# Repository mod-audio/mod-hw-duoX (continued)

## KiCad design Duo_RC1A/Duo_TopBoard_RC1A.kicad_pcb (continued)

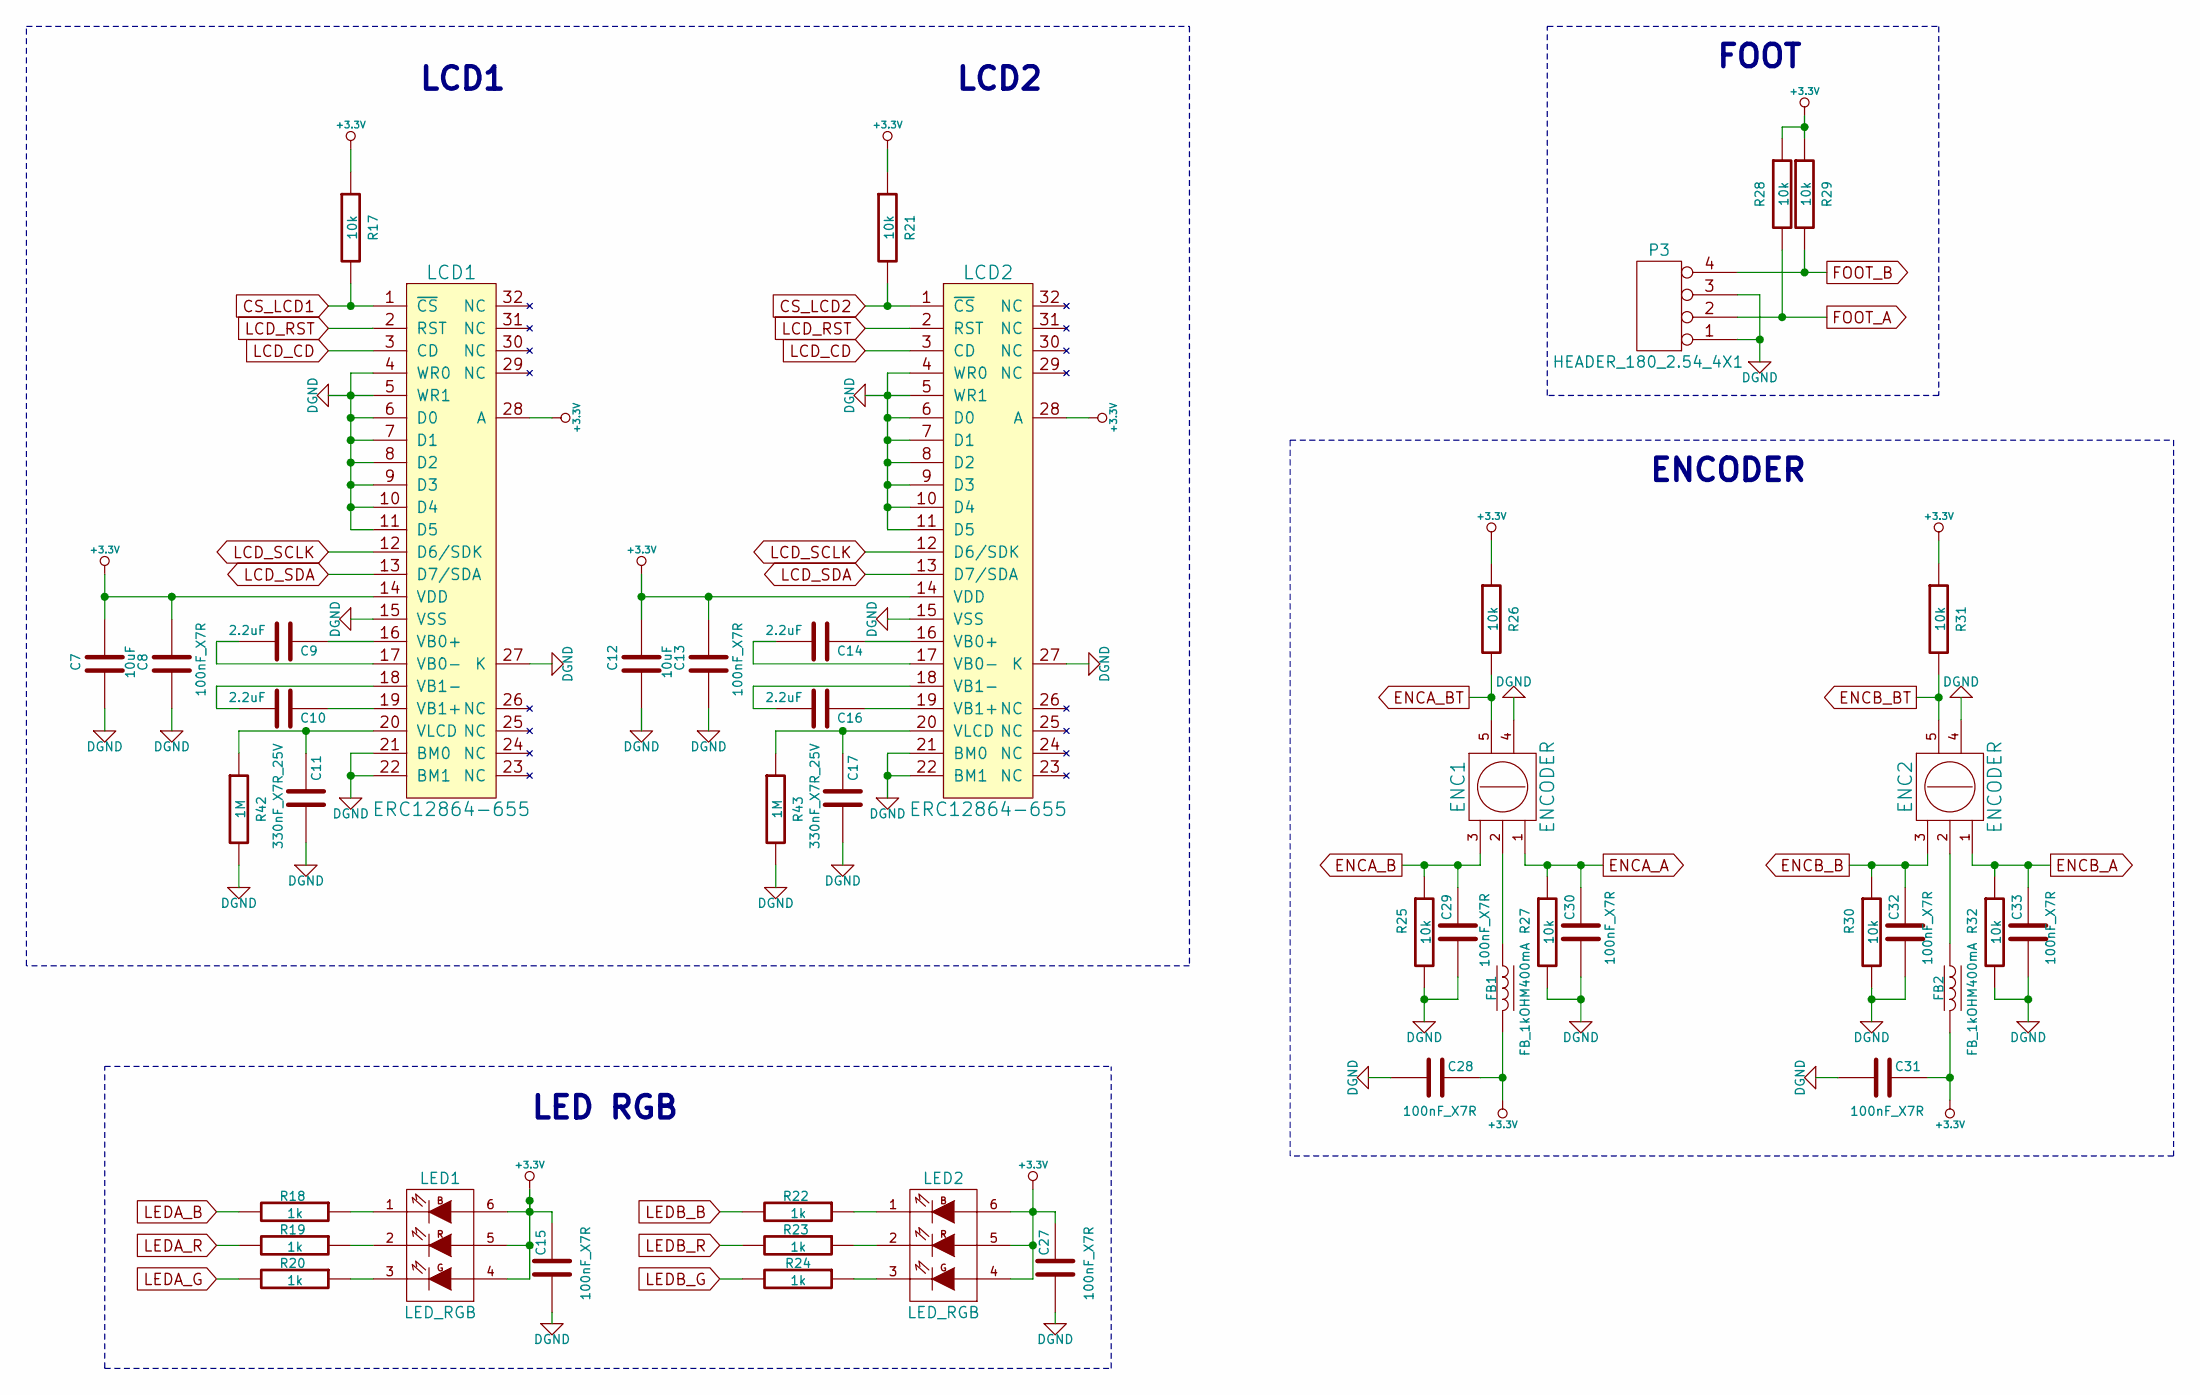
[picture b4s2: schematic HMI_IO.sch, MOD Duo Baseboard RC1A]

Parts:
C7, C12: 10uF; SM0603
C8, C13, C15, C27, C28, C29, C30, C31, C32, C33: 100nF_X7R; SM0603
C9, C10, C14, C16: 2.2uF; SM0603
C11, C17: 330nF_X7R_25V; SM0603
ENC1, ENC2: ENCODER; ENCODER_PEC11R-4xxxF-Sxxxx
FB1, FB2: FB_1kOHM400mA; SM0805
LCD1, LCD2: ERC12864-655
LED1, LED2: LED_RGB; LED_CLRTB_GFSF_1
P3: HEADER_180_2.54_4X1; Pin_Header_180_2.54_1x4
R17, R21, R25, R26, R27, R28, R29, R30, R31, R32: 10k; SM0603
R18, R19, R20, R22, R23, R24: 1k; SM0603
R42, R43: 1M; SM0603

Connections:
+3.3V: C7.1, C8.1, C12.1, C13.1, C15.1, C27.1, C28.1, C31.1, FB1.1, FB2.1, LCD1.14 (VDD), LCD1.28 (A), LCD2.14 (VDD), LCD2.28 (A), LED1.4 (KB), LED1.5 (KG), LED1.6 (KR), LED2.4 (KB), LED2.5 (KG), LED2.6 (KR), R17.1, R21.1, R26.1, R28.1, R29.1, R31.1; also elsewhere on the board
CS_LCD1: LCD1.1 (~CS), R17.2; also elsewhere on the board
CS_LCD2: LCD2.1 (~CS), R21.2; also elsewhere on the board
DGND: C7.2, C8.2, C11.2, C12.2, C13.2, C15.2, C17.2, C27.2, C28.2, C29.2, C30.2, C31.2, C32.2, C33.2, ENC1.4, ENC2.4, LCD1.4 (WR0), LCD1.5 (WR1), LCD1.6 (D0), LCD1.7 (D1), LCD1.8 (D2), LCD1.9 (D3), LCD1.10 (D4), LCD1.11 (D5), LCD1.15 (VSS), LCD1.21 (BM0), LCD1.22 (BM1), LCD1.27 (K), LCD2.4 (WR0), LCD2.5 (WR1), LCD2.6 (D0), LCD2.7 (D1), LCD2.8 (D2), LCD2.9 (D3), LCD2.10 (D4), LCD2.11 (D5), LCD2.15 (VSS), LCD2.21 (BM0), LCD2.22 (BM1), LCD2.27 (K), P3.1, P3.3, R25.2, R27.2, R30.2, R32.2, R42.2, R43.2; also elsewhere on the board
ENCA_A: C30.1, ENC1.1, R27.1; also elsewhere on the board
ENCA_B: C29.1, ENC1.3, R25.1; also elsewhere on the board
ENCA_BT: ENC1.5, R26.2; also elsewhere on the board
ENCB_A: C33.1, ENC2.1, R32.1; also elsewhere on the board
ENCB_B: C32.1, ENC2.3, R30.1; also elsewhere on the board
ENCB_BT: ENC2.5, R31.2; also elsewhere on the board
FOOT_A: P3.2, R28.2; also elsewhere on the board
FOOT_B: P3.4, R29.2; also elsewhere on the board
LCD_CD: LCD1.3 (CD), LCD2.3 (CD); also elsewhere on the board
LCD_RST: LCD1.2 (RST), LCD2.2 (RST); also elsewhere on the board
LCD_SCLK: LCD1.12 (D6/SDK), LCD2.12 (D6/SDK); also elsewhere on the board
LCD_SDA: LCD1.13 (D7/SDA), LCD2.13 (D7/SDA); also elsewhere on the board
LEDA_B: R18.2; also elsewhere on the board
LEDA_G: R20.2; also elsewhere on the board
LEDA_R: R19.2; also elsewhere on the board
LEDB_B: R22.2; also elsewhere on the board
LEDB_G: R24.2; also elsewhere on the board
LEDB_R: R23.2; also elsewhere on the board
unnamed: C9.1, LCD1.16 (VB0+)
unnamed: C9.2, LCD1.17 (VB0-)
unnamed: C10.1, LCD1.19 (VB1+)
unnamed: C10.2, LCD1.18 (VB1-)
unnamed: C11.1, LCD1.20 (VLCD), R42.1
unnamed: C14.1, LCD2.16 (VB0+)
unnamed: C14.2, LCD2.17 (VB0-)
unnamed: C16.1, LCD2.19 (VB1+)
unnamed: C16.2, LCD2.18 (VB1-)
unnamed: C17.1, LCD2.20 (VLCD), R43.1
unnamed: ENC1.2, FB1.2
unnamed: ENC2.2, FB2.2
unnamed: LED1.1 (AR), R18.1
unnamed: LED1.2 (AG), R19.1
unnamed: LED1.3 (AB), R20.1
unnamed: LED2.1 (AR), R22.1
unnamed: LED2.2 (AG), R23.1
unnamed: LED2.3 (AB), R24.1

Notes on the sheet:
LED RGB
ENCODER
FOOT
LCD2
LCD1

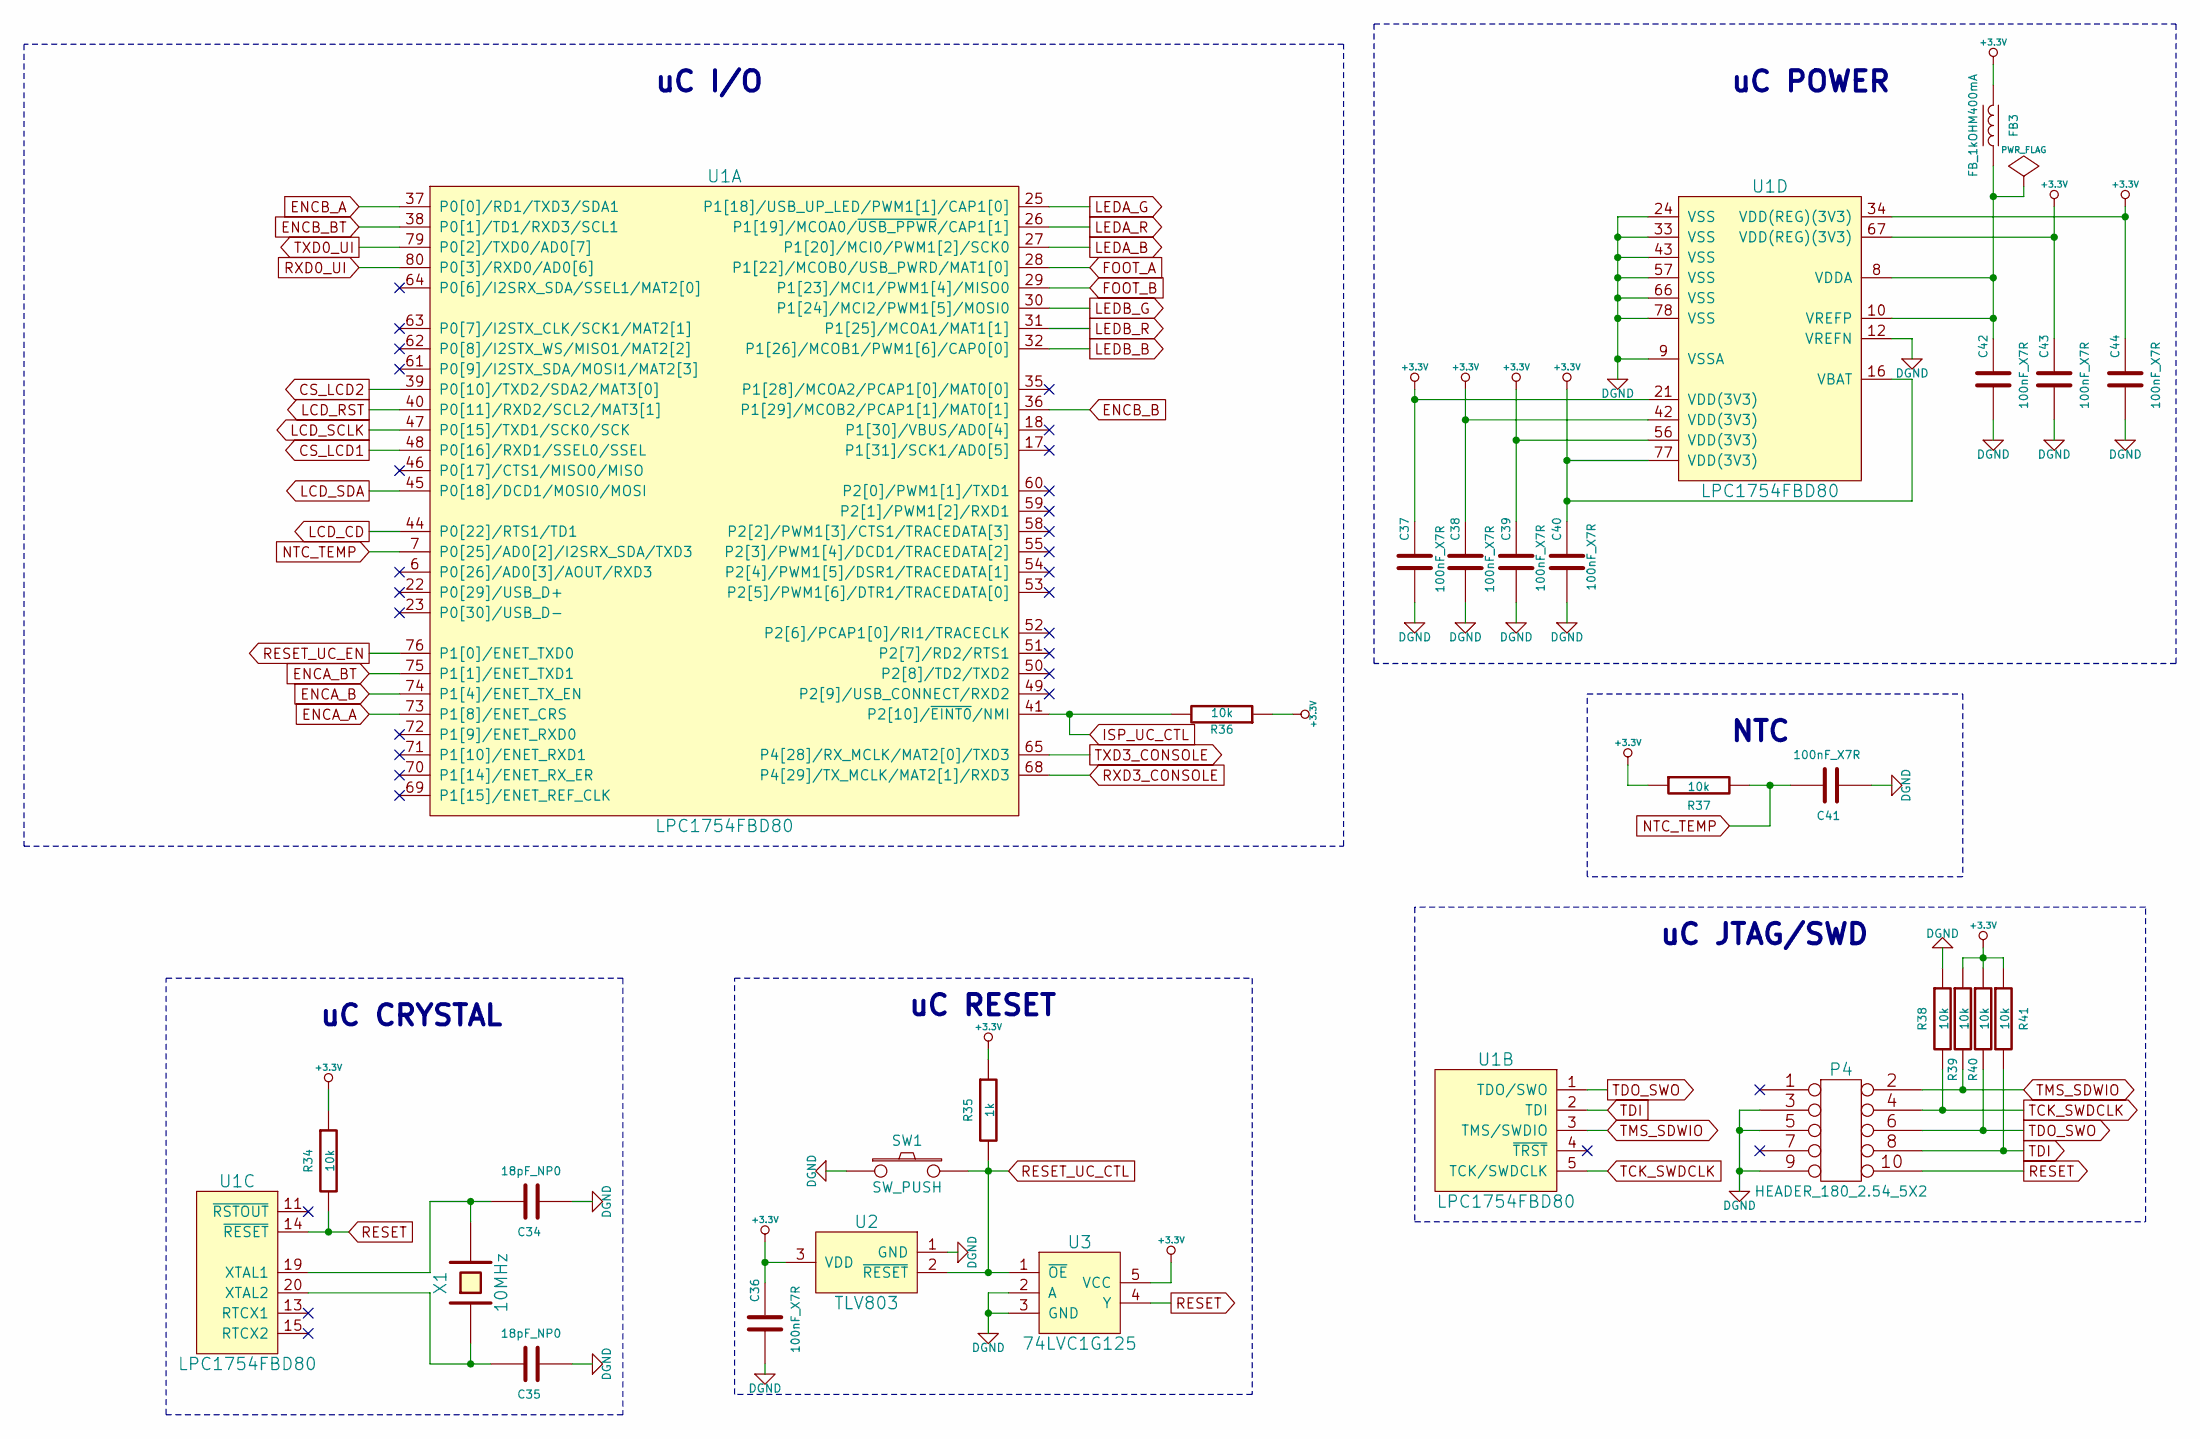
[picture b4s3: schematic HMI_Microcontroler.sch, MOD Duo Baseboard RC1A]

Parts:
C34, C35: 18pF_NP0; SM0603
C36, C37, C38, C39, C40, C41, C42, C43, C44: 100nF_X7R; SM0603
FB3: FB_1kOHM400mA; SM0805
P4: HEADER_180_2.54_5X2; Pin_Header_180_2.54_2x5
R34, R36, R37, R38, R39, R40, R41: 10k; SM0603
R35: 1k; SM0603
SW1: SW_PUSH; SWITCH_SMD_FSMSM
U1: LPC1754FBD80; LQFP80
U2: TLV803; SOT23
U3: 74LVC1G125; SOT353
X1: 10MHz; HC_49US

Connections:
+3.3V: C36.1, C37.1, C38.1, C39.1, C40.1, C43.1, C44.1, FB3.1, R34.1, R35.1, R36.1, R37.1, R39.1, R40.1, R41.1, U1.16 (VBAT), U1.21 (VDD(3V3)), U1.34 (VDD(REG)(3V3)), U1.42 (VDD(3V3)), U1.56 (VDD(3V3)), U1.67 (VDD(REG)(3V3)), U1.77 (VDD(3V3)), U2.3 (VDD), U3.5 (VCC); also elsewhere on the board
CS_LCD1: U1.48 (P0[16]/RXD1/SSEL0/SSEL); also elsewhere on the board
CS_LCD2: U1.39 (P0[10]/TXD2/SDA2/MAT3[0]); also elsewhere on the board
DGND: C34.2, C35.2, C36.2, C37.2, C38.2, C39.2, C40.2, C41.2, C42.2, C43.2, C44.2, P4.3, P4.5, P4.9, R38.1, SW1.1, U1.9 (VSSA), U1.12 (VREFN), U1.24 (VSS), U1.33 (VSS), U1.43 (VSS), U1.57 (VSS), U1.66 (VSS), U1.78 (VSS), U2.1 (GND), U3.2 (A), U3.3 (GND); also elsewhere on the board
ENCA_A: U1.73 (P1[8]/ENET_CRS); also elsewhere on the board
ENCA_B: U1.74 (P1[4]/ENET_TX_EN); also elsewhere on the board
ENCA_BT: U1.75 (P1[1]/ENET_TXD1); also elsewhere on the board
ENCB_A: U1.37 (P0[0]/RD1/TXD3/SDA1); also elsewhere on the board
ENCB_B: U1.36 (P1[29]/MCOB2/PCAP1[1]/MAT0[1]); also elsewhere on the board
ENCB_BT: U1.38 (P0[1]/TD1/RXD3/SCL1); also elsewhere on the board
FOOT_A: U1.28 (P1[22]/MCOB0/USB_PWRD/MAT1[0]); also elsewhere on the board
FOOT_B: U1.29 (P1[23]/MCI1/PWM1[4]/MISO0); also elsewhere on the board
ISP_UC_CTL: R36.2, U1.41 (P2[10]/~EINT0~/NMI); also elsewhere on the board
LCD_CD: U1.44 (P0[22]/RTS1/TD1); also elsewhere on the board
LCD_RST: U1.40 (P0[11]/RXD2/SCL2/MAT3[1]); also elsewhere on the board
LCD_SCLK: U1.47 (P0[15]/TXD1/SCK0/SCK); also elsewhere on the board
LCD_SDA: U1.45 (P0[18]/DCD1/MOSI0/MOSI); also elsewhere on the board
LEDA_B: U1.27 (P1[20]/MCI0/PWM1[2]/SCK0); also elsewhere on the board
LEDA_G: U1.25 (P1[18]/USB_UP_LED/PWM1[1]/CAP1[0]); also elsewhere on the board
LEDA_R: U1.26 (P1[19]/MCOA0/~USB_PPWR~/CAP1[1]); also elsewhere on the board
LEDB_B: U1.32 (P1[26]/MCOB1/PWM1[6]/CAP0[0]); also elsewhere on the board
LEDB_G: U1.30 (P1[24]/MCI2/PWM1[5]/MOSI0); also elsewhere on the board
LEDB_R: U1.31 (P1[25]/MCOA1/MAT1[1]); also elsewhere on the board
NTC_TEMP: C41.1, R37.2, U1.7 (P0[25]/AD0[2]/I2SRX_SDA/TXD3); also elsewhere on the board
unnamed: C34.1, U1.19 (XTAL1), X1.2
unnamed: C35.1, U1.20 (XTAL2), X1.1
unnamed: C42.1, FB3.2, U1.8 (VDDA), U1.10 (VREFP)
RESET: P4.10, R34.2, U1.14 (~RESET), U3.4 (Y)
RESET_UC_CTL: R35.2, SW1.2, U2.2 (~RESET), U3.1 (~OE); also elsewhere on the board
RESET_UC_EN: U1.76 (P1[0]/ENET_TXD0); also elsewhere on the board
RXD0_UI: U1.80 (P0[3]/RXD0/AD0[6]); also elsewhere on the board
RXD3_CONSOLE: U1.68 (P4[29]/TX_MCLK/MAT2[1]/RXD3); also elsewhere on the board
TCK_SWDCLK: P4.4, R38.2, U1.5 (TCK/SWDCLK)
TDI: P4.8, R41.2, U1.2 (TDI)
TDO_SWO: P4.6, R40.2, U1.1 (TDO/SWO)
TMS_SDWIO: P4.2, R39.2, U1.3 (TMS/SWDIO)
TXD0_UI: U1.79 (P0[2]/TXD0/AD0[7]); also elsewhere on the board
TXD3_CONSOLE: U1.65 (P4[28]/RX_MCLK/MAT2[0]/TXD3); also elsewhere on the board

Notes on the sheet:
uC JTAG/SWD
uC RESET
uC CRYSTAL
uC POWER
uC I/O
NTC

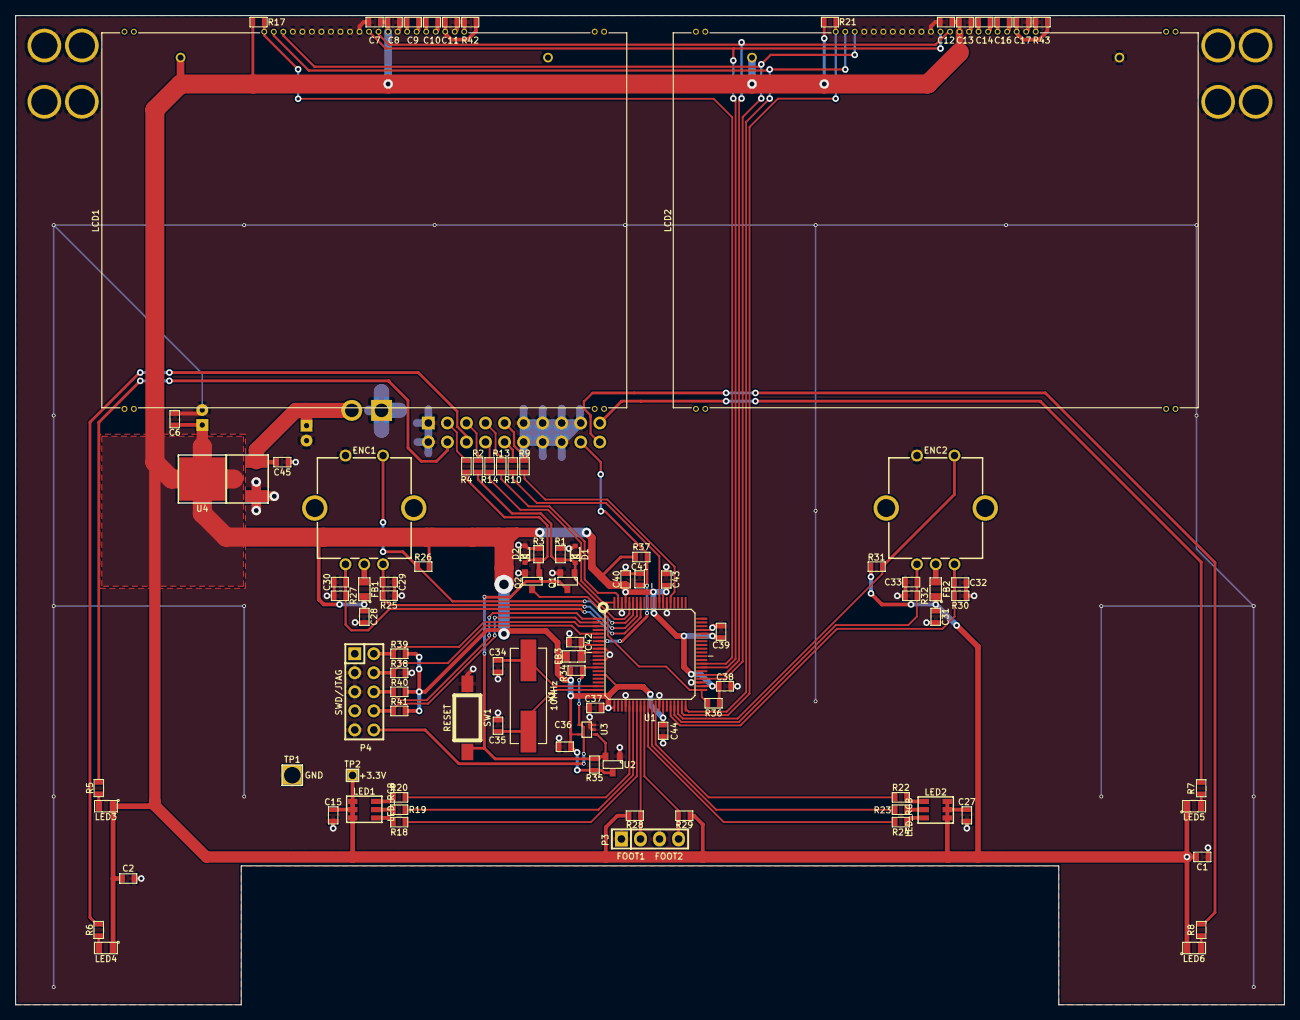
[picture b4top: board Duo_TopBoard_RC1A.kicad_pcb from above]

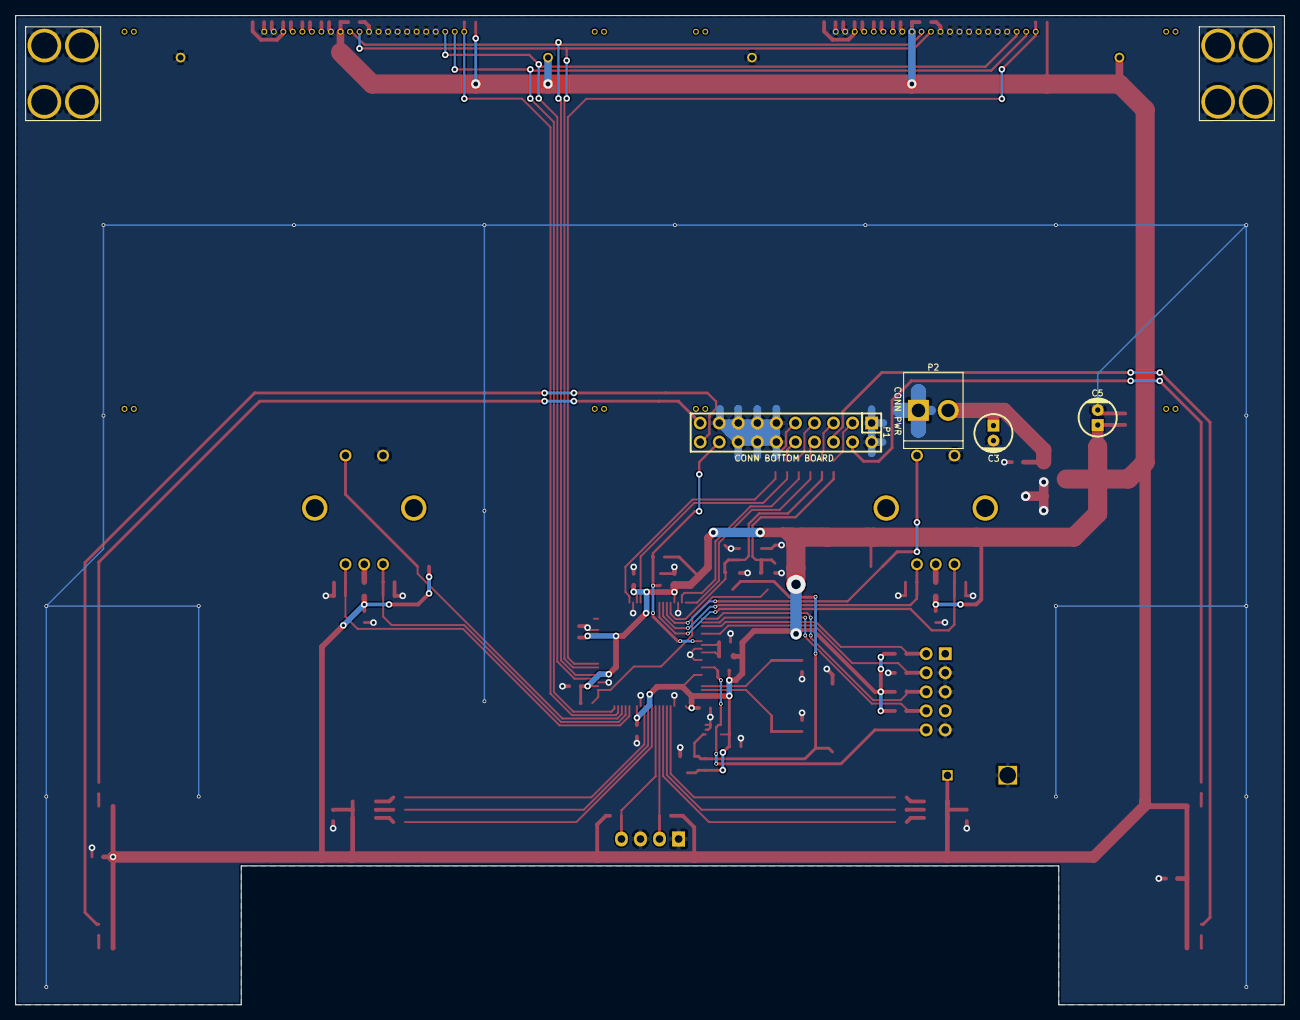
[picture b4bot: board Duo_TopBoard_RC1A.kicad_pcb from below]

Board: 2 copper layers, 169.2 x 131.9 mm, 104 parts (6 on the bottom side), 72 nets.

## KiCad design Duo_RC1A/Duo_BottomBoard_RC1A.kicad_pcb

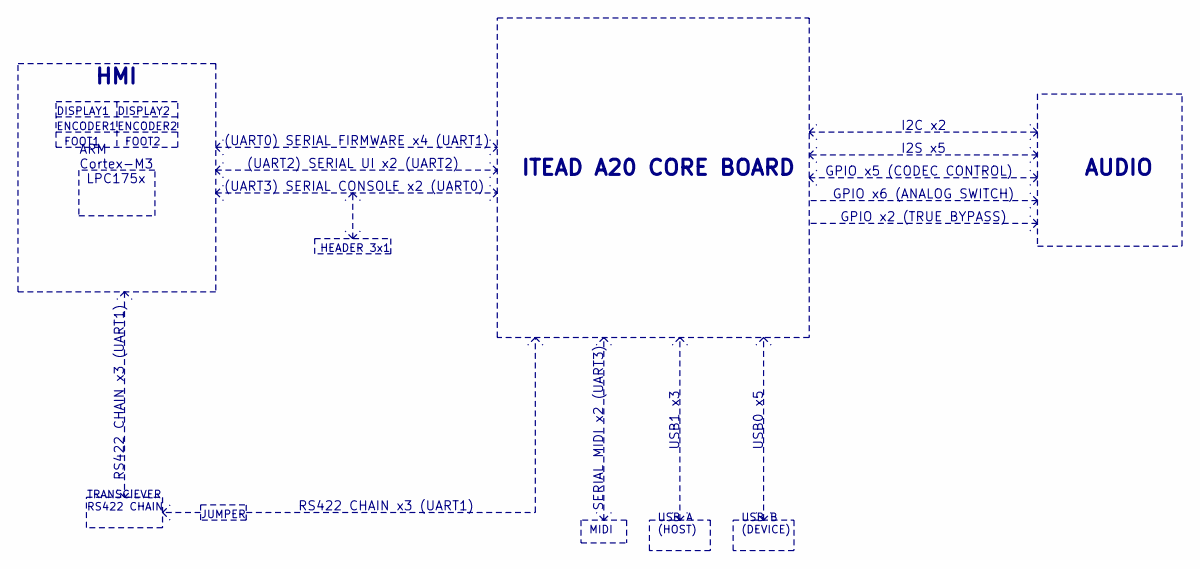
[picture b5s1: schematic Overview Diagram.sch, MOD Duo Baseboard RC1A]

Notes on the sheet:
ITEAD A20 CORE BOARD
ARM Cortex-M3 LPC175x
I2S x5
(UART0) SERIAL FIRMWARE x4 (UART1)
(UART2) SERIAL UI x2 (UART2)
HEADER 3x1
RS422 CHAIN x3 (UART1)
I2C x2
GPIO x6 (ANALOG SWITCH)
GPIO x2 (TRUE BYPASS)
(UART3) SERIAL CONSOLE x2 (UART0)
MIDI
SERIAL MIDI x2 (UART3)
DISPLAY1
DISPLAY2
FOOT1
FOOT2
ENCODER1
ENCODER2
HMI
TRANSCIEVER RS422 CHAIN
USB A (HOST)
USB B (DEVICE)
USB1 x3
USB0 x5
GPIO x5 (CODEC CONTROL)
AUDIO
JUMPER

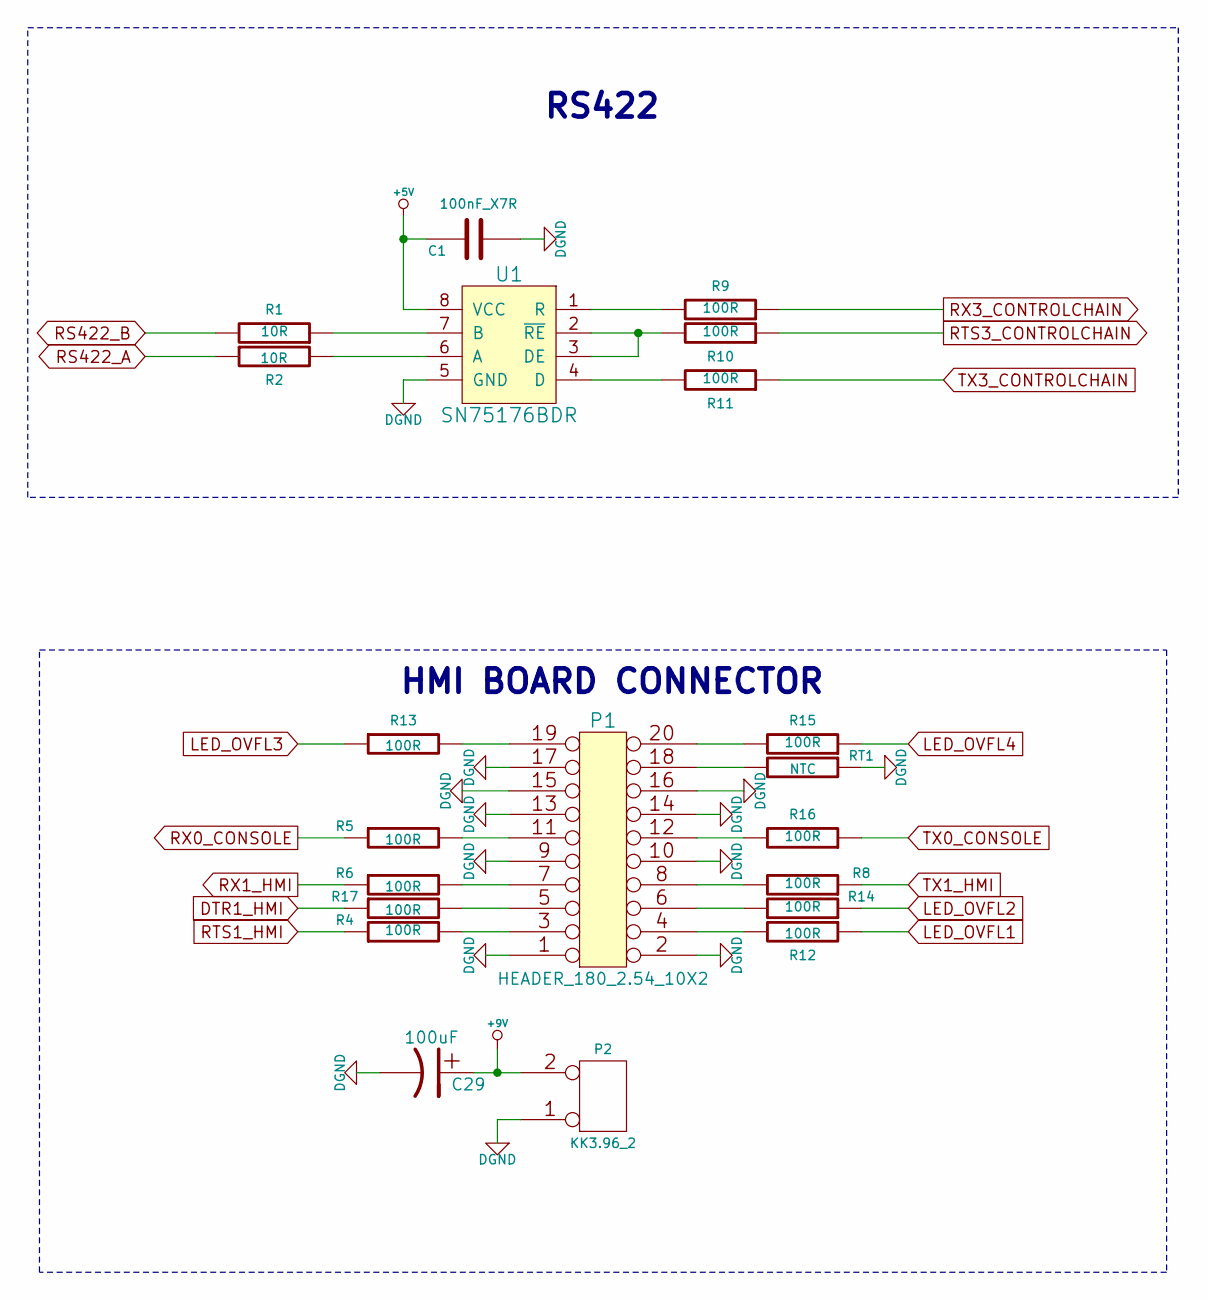
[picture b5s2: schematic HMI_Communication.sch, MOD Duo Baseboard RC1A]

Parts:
C1: 100nF_X7R; SM0603
C29: 100uF; Capacitor5x11RM2
P1: HEADER_180_2.54_10X2; Pin_Header_180_2.54_2x10
P2: KK3.96_2; KK3.96_2PIN
R1, R2: 10R; SM0805
R4, R5, R6, R8, R9, R10, R11, R12, R13, R14, R15, R16, R17: 100R; SM0603
RT1: NTC; SM0805
U1: SN75176BDR; SOIC8_E

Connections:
+5V: C1.2, U1.8 (VCC); also elsewhere on the board
+9V: C29.1, P2.2 (PM); also elsewhere on the board
DGND: C1.1, C29.2, P1.1, P1.2, P1.9, P1.10, P1.13, P1.14, P1.15, P1.16, P1.17, P2.1, RT1.1, U1.5 (GND); also elsewhere on the board
DTR1_HMI: R17.1; also elsewhere on the board
LED_OVFL1: R12.1; also elsewhere on the board
LED_OVFL2: R14.1; also elsewhere on the board
LED_OVFL3: R13.1; also elsewhere on the board
LED_OVFL4: R15.1; also elsewhere on the board
unnamed: P1.3, R4.2
unnamed: P1.4, R12.2
unnamed: P1.5, R17.2
unnamed: P1.6, R14.2
unnamed: P1.7, R6.2
unnamed: P1.8, R8.2
unnamed: P1.11, R5.2
unnamed: P1.12, R16.2
unnamed: P1.18, RT1.2
unnamed: P1.19, R13.2
unnamed: P1.20, R15.2
unnamed: R1.1, U1.7 (B)
unnamed: R2.2, U1.6 (A)
unnamed: R9.2, U1.1 (R)
unnamed: R10.2, U1.2 (~RE), U1.3 (DE)
unnamed: R11.2, U1.4 (D)
RS422_A: R2.1; also elsewhere on the board
RS422_B: R1.2; also elsewhere on the board
RTS1_HMI: R4.1; also elsewhere on the board
RTS3_CONTROLCHAIN: R10.1; also elsewhere on the board
RX0_CONSOLE: R5.1; also elsewhere on the board
RX1_HMI: R6.1; also elsewhere on the board
RX3_CONTROLCHAIN: R9.1; also elsewhere on the board
TX0_CONSOLE: R16.1; also elsewhere on the board
TX1_HMI: R8.1; also elsewhere on the board
TX3_CONTROLCHAIN: R11.1; also elsewhere on the board

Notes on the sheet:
RS422
HMI BOARD CONNECTOR

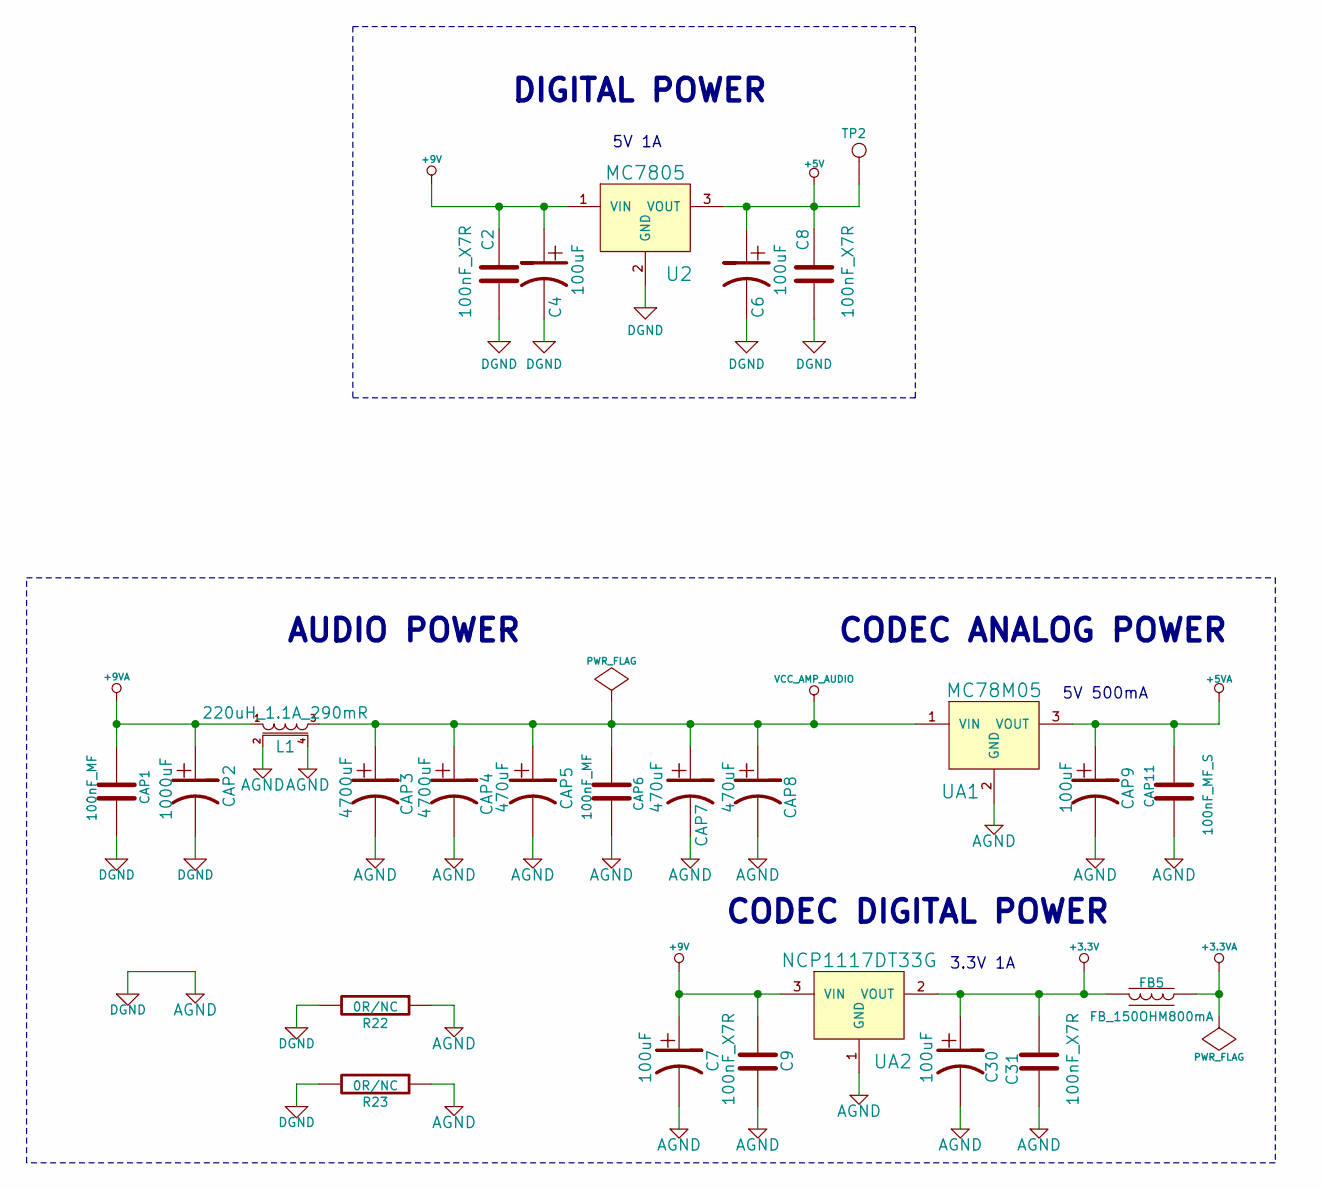
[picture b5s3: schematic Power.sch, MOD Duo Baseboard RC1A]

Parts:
C2, C8, C9, C31: 100nF_X7R; SM0603
C4, C6, C7, C30: 100uF; Capacitor5x11RM2
CAP1, CAP6: 100nF_MF; CAP_FILM_12.6X4.5_L10
CAP2: 1000uF; Capacitor10x21RM5
CAP3, CAP4: 4700uF; Capacitor16x25RM7.5
CAP5, CAP7, CAP8: 470uF; Capacitor8x13RM3.5
CAP9: 100uF; Capacitor5x11RM2
CAP11: 100nF_MF_S; CapacitorMetalFilm_7.2x2.5MM_P5MM
FB5: FB_150OHM800mA; SM0805
L1: 220uH_1.1A_290mR; IND_RAD_10MM_4P
R22, R23: 0R/NC; SM0805
TP2: TEST_POINT_1MM; TESTPOINT_1MM
U2: MC7805; DPAK(369C)
UA1: MC78M05; DPAK(369C)
UA2: NCP1117DT33G; DPAK(369C)

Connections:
+3.3V: C30.1, C31.1, FB5.1, UA2.2 (VOUT); also elsewhere on the board
+3.3VA: FB5.2; also elsewhere on the board
+5V: C6.1, C8.1, TP2.1, U2.3 (VOUT); also elsewhere on the board
+5VA: CAP9.1, CAP11.1, UA1.3 (VOUT); also elsewhere on the board
+9V: C2.1, C4.1, C7.1, C9.1, U2.1 (VIN), UA2.3 (VIN); also elsewhere on the board
+9VA: CAP1.1, CAP2.1, L1.1; also elsewhere on the board
DGND: C2.2, C4.2, C6.2, C7.2, C8.2, C9.2, C30.2, C31.2, CAP1.2, CAP2.2, CAP3.2, CAP4.2, CAP5.2, CAP6.2, CAP7.2, CAP8.2, CAP9.2, CAP11.2, L1.2, L1.4, R22.1, R22.2, R23.1, R23.2, U2.2 (GND), UA1.2 (GND), UA2.1 (GND); also elsewhere on the board
VCC_AMP_AUDIO: CAP3.1, CAP4.1, CAP5.1, CAP6.1, CAP7.1, CAP8.1, L1.3, UA1.1 (VIN); also elsewhere on the board

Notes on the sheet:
AUDIO POWER
5V 500mA
3.3V 1A
CODEC ANALOG POWER
5V 1A
DIGITAL POWER
CODEC DIGITAL POWER
